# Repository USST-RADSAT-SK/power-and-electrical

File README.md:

# power-and-electrical

## How to Download GitBash
  
  Gitbash is a terminal that you use to execute "git" commands and its highly recommended that you download it 
  
  Use the following link
  https://git-scm.com/downloads
  
## How to Copy a Repo

  Make a folder on your local drive (I make a folder on my desktop)
  
  go into that folder and right click and open gitbash at that location
  
  find the green button in the github that says "Code"
  
  click and copy the URL
  
  go back into the gitbash enter
  
  "git clone [URL]" 

  Now if you want to make changes to a file please make a branch 
  
## How To View a Branch

  Say you want to do a quick check on the progress for the PCB board
  
  use the following commands in git bash
  
  "git checkout [name of branch]"
  
  In the case that KiCad is not updating automatically use the following procedure:
  
  - open project file with "open with..." in file directory 

  If you quickly want to check when the last changes were done to a branch use
  
  "git log"
  
  scroll up & you will see the most recent commit and who did it
  
## How To Make a Branch
  
  a branch is like a copy of files that you can edit on your local drive where you dont have to worry about messing up the main code
  
  make sure you are in the right directory
  
  "git branch [name of the branch]"

  keep the name of the branch short and sweet no need to make it complitcated

## How to Commit a Change

  Once gitbash is opened you want to make sure you are in the right file directory you want to use the command 
  
  "git status"
  
  to check if you saved your files (it will show up as red)
  
  "Git add [filename]"
  
  this will prepare your file to be commited
  
  "git status"
  
  the file name should be green now
  
  "git commit -m "[changes you made as a comment]" "
  
  this will commit your changes 
  
  "git push"
  
  this will save your changes into the branch

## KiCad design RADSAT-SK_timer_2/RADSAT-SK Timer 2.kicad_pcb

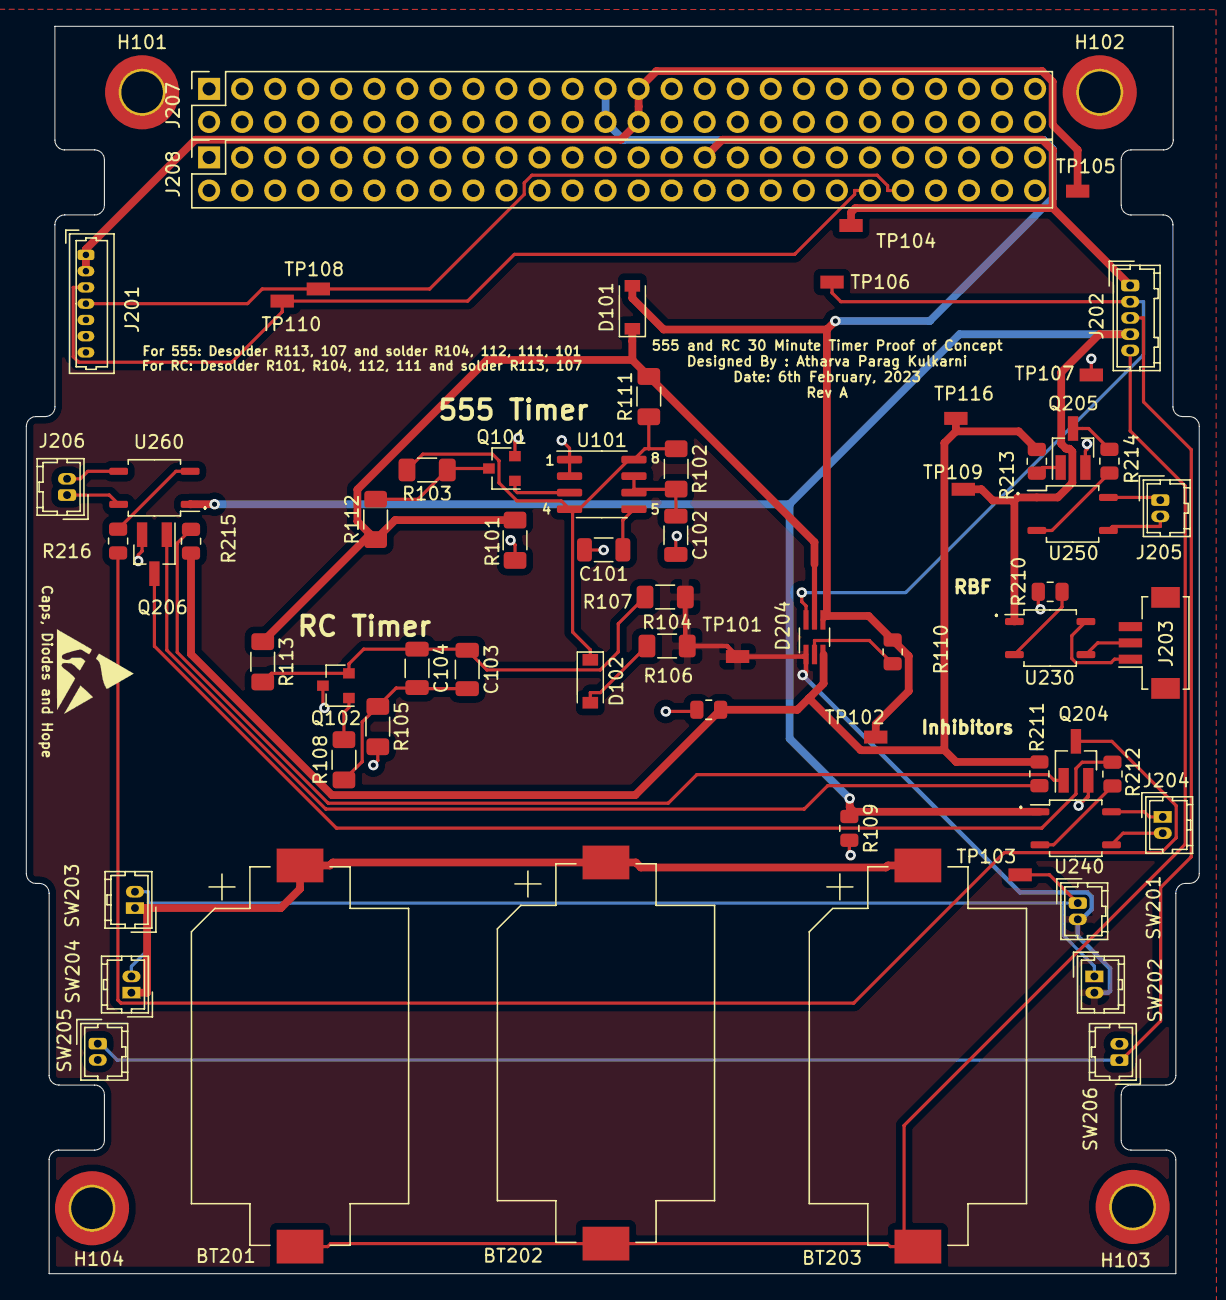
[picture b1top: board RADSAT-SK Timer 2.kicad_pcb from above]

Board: 2 copper layers, 90.2 x 95.9 mm, 69 parts (0 on the bottom side), 43 nets.

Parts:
BT201, BT202, BT203: Battery_Cell; BatteryHolder_Keystone_1060_1x2032
C101: 10nF; C_1206_3216Metric
C102, C103, C104: 600uF; C_1206_3216Metric
D101, D102: SBR80520LT1G; D_SOD-123
D204: BAT54CDW; SOT-363_SC-70-6_Handsoldering
H101, H102, H103, H104: MountingHole; MountingHole_3.2mm_M3_ISO7380_Pad_TopBottom
J201: Conn_01x07; Molex_PicoBlade_53047-0710_1x07_P1.25mm_Vertical
J202: Conn_01x05_Female; Hirose_DF13-05P-1.25DSA_1x05_P1.25mm_Vertical
J203: Conn_01x03; Hirose_DF13C_CL535-0403-5-51_1x03-1MP_P1.25mm_Vertical
J204, J205, J206: Conn_01x02; Hirose_DF13-02P-1.25DSA_1x02_P1.25mm_Vertical
J207, J208: Conn_02x26_Odd_Even; PinSocket_2x26_P2.54mm_Vertical
Q101: 2N7002E; SOT-23
Q102: DSS4240T-7; SOT-23
Q204, Q205, Q206: IRLML2060; SOT-23_Handsoldering
R101: 10k; R_1206_3216Metric_Pad1.30x1.75mm_HandSolder
R102, R108: 3M; R_1206_3216Metric_Pad1.30x1.75mm_HandSolder
R103: 1M; R_1206_3216Metric_Pad1.30x1.75mm_HandSolder
R104, R105, R107, R111, R112, R113: 0; R_1206_3216Metric_Pad1.30x1.75mm_HandSolder
R106, R109: 1M; R_0805_2012Metric
R110: 40; R_0805_2012Metric
R210: 320; R_0805_2012Metric
R211, R213, R215: 25; R_0805_2012Metric
R212, R214, R216: 260; R_0805_2012Metric
SW201, SW202, SW203, SW204, SW205, SW206: SW_Push; Hirose_DF13-02P-1.25DSA_1x02_P1.25mm_Vertical
TP101, TP102, TP103, TP104, TP105, TP106, TP107, TP108, TP109, TP110, TP116: TestPoint; HARWIN_S2761-46R
U101: TLC555CDR; SOIC-8_3.9x4.9mm_P1.27mm
U230, U240, U250, U260: CPC1114N; SOP-4_3.8x4.1mm_P2.54mm

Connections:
+3V3: J201.1, J201.2, J207.27, J207.28, TP105.1
+5V: D101.2, D204.4, J207.25, J207.26, R110.2, TP102.1
+BATT: D204.1, R104.2, R107.2, SW201.2, SW202.2, TP101.1
/Inhib_in: D204.3, R106.1, R211.1, R213.1, R215.1, TP116.1
A: BT201.1, BT202.1, BT203.1, SW203.1, SW204.1
GND: C101.2, C102.2, J201.5, J201.6, J201.7, J207.29, J207.30, J207.32, Q101.2, Q102.3, Q204.2, Q205.2, Q206.2, R101.2, R105.2, R106.2, R109.2, R210.2, SW205.2, SW206.2, TP107.1, U101.1, U101.2
I2C_CLK: J201.4, J208.44, TP108.1
I2C_DATA: J201.3, J208.42, TP110.1
InhibV+: J202.4, R109.1, TP109.1, U230.1, U240.1, U250.1, U260.1
Inhib_EN: D101.1, D204.5, R101.1, R111.2, R112.1, R113.1
unnamed: BT201.2, BT202.2, BT203.2, J202.5
unnamed: C101.1, U101.5
unnamed: C102.1, R102.2, U101.6, U101.7
unnamed: C103.1, C104.1, Q102.2, R107.1, R113.2
unnamed: C103.2, C104.2, R105.1, R108.1
unnamed: D102.1, R102.1, R103.2, R111.1, U101.4, U101.8
unnamed: D102.2, R104.1
unnamed: D204.2, R110.1
unnamed: D204.6, J202.2, TP106.1
unnamed: J202.3, SW205.1, SW206.1
unnamed: J203.1, U230.4
unnamed: J203.2, U230.3
unnamed: J204.1, U240.4
unnamed: J204.2, U240.3
unnamed: J205.1, U250.4
unnamed: J205.2, U250.3
unnamed: J206.1, U260.4
unnamed: J206.2, U260.3
unnamed: Q101.1, U101.3
unnamed: Q101.3, R103.1, R112.2
unnamed: Q102.1, R108.2
unnamed: Q204.1, R215.2
unnamed: Q204.3, R216.2
unnamed: Q205.1, R213.2
unnamed: Q205.3, R214.2
unnamed: Q206.1, R211.2
unnamed: Q206.3, R212.2
unnamed: R210.1, U230.2
unnamed: R212.1, U240.2
unnamed: R214.1, U250.2
unnamed: R216.1, U260.2
unnamed: SW201.1, SW202.1, SW203.2, SW204.2, TP103.1
USB_Charge: J202.1, J208.31, TP104.1

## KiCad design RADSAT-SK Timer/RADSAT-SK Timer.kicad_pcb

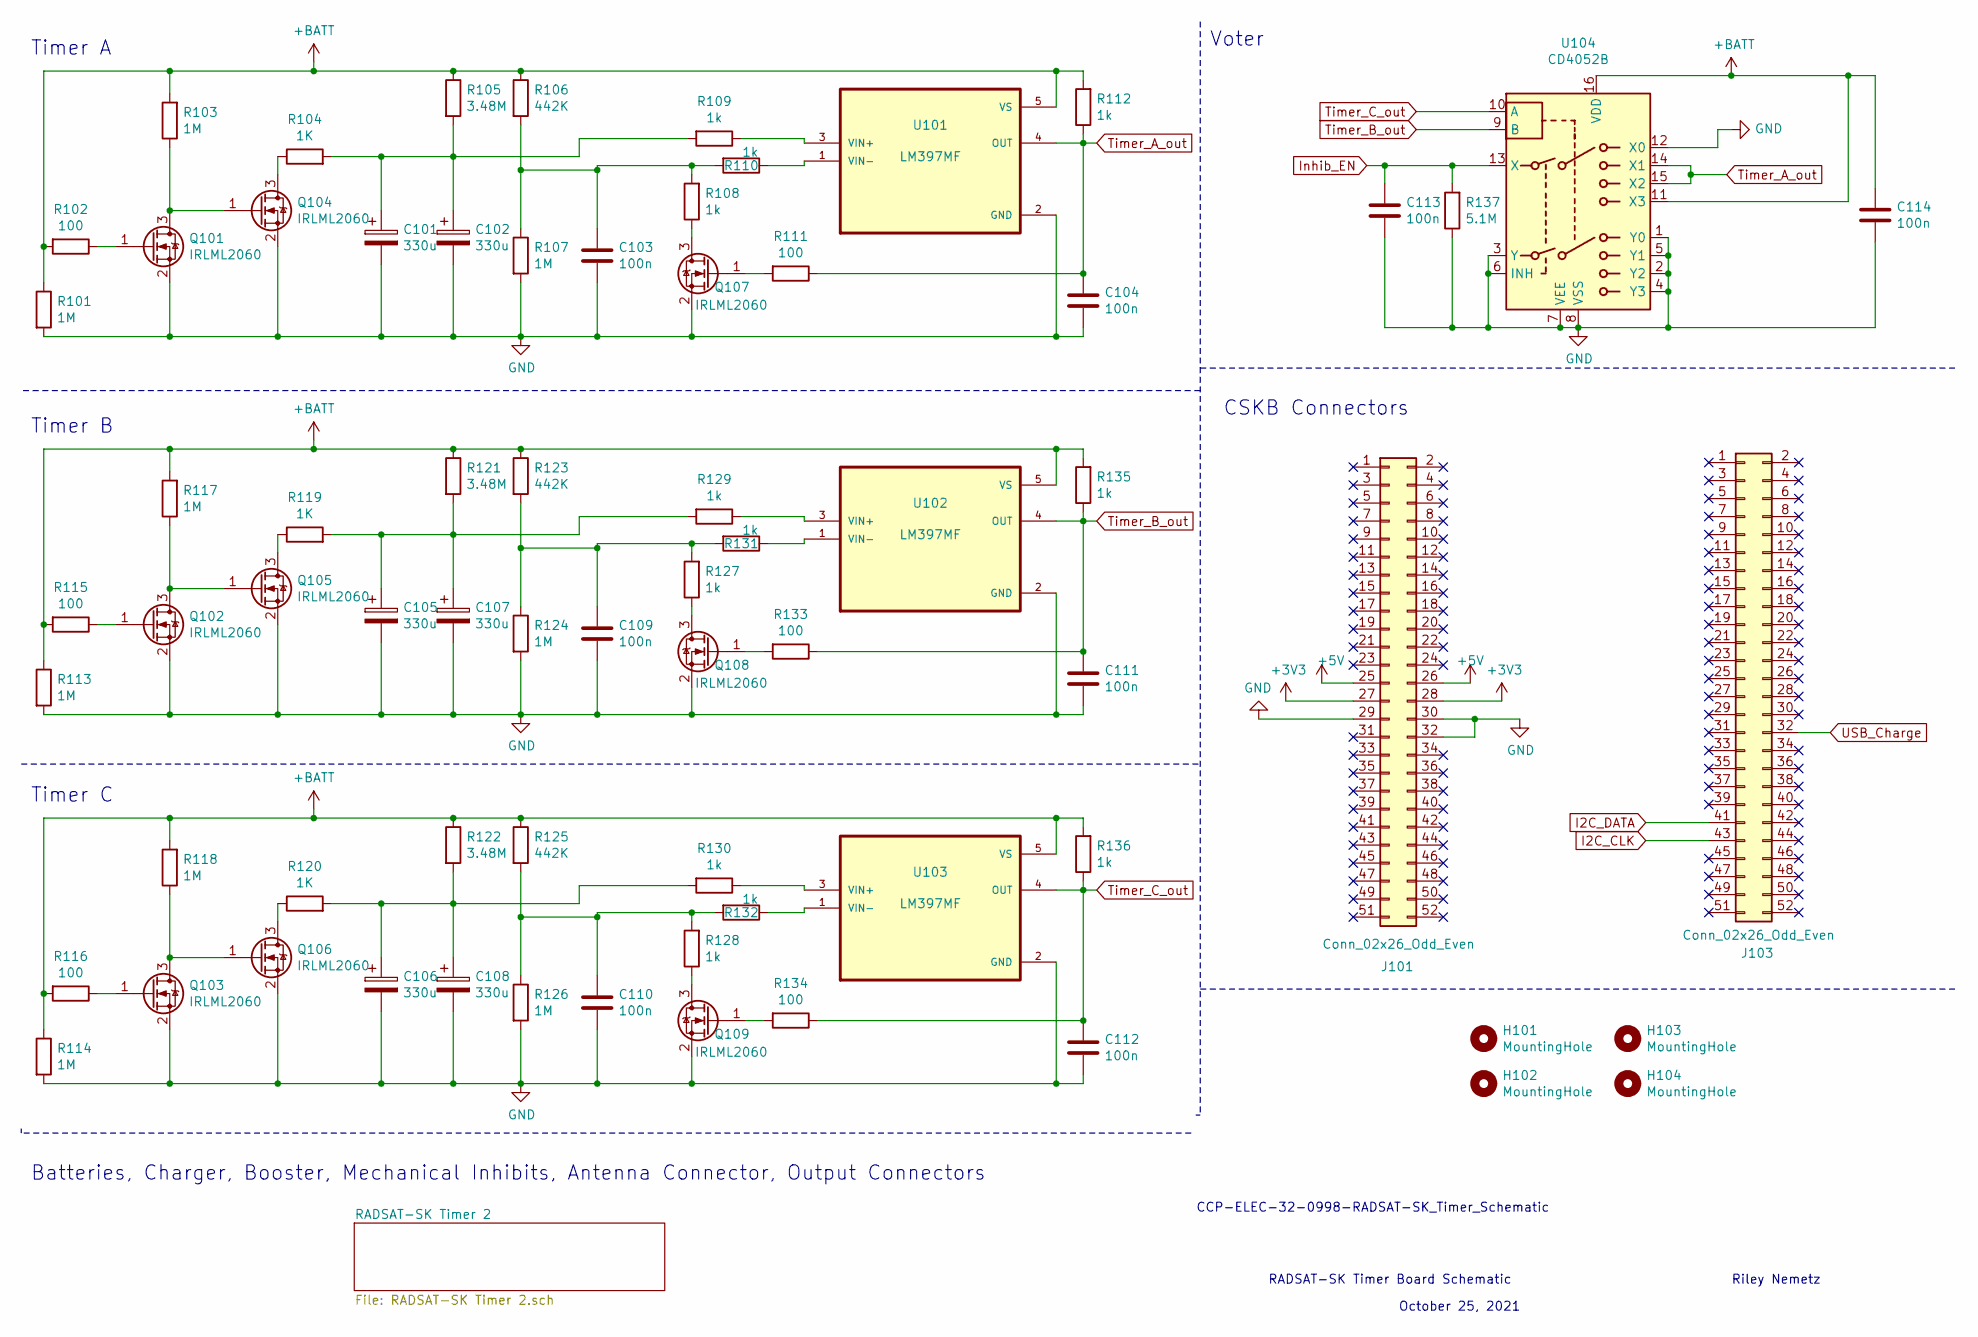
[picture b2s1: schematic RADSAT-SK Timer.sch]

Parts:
C101, C102, C105, C106, C107, C108: 330u; CP_EIA-7343-30_AVX-N_Pad2.25x2.55mm_HandSolder
C103, C104, C109, C110, C111, C112, C113, C114: 100n; C_0805_2012Metric
H101, H102, H103, H104: MountingHole; MountingHole_3.2mm_M3_ISO7380_Pad_TopBottom
J101, J103: Conn_02x26_Odd_Even; PinSocket_2x26_P2.54mm_Vertical
Q101, Q102, Q103, Q104, Q105, Q106, Q107, Q108, Q109: IRLML2060; SOT-23_Handsoldering
R101, R103, R107, R113, R114, R117, R118, R124, R126: 1M; R_0805_2012Metric
R102, R111, R115, R116, R133, R134: 100; R_0805_2012Metric
R104, R119, R120: 1K; R_0805_2012Metric
R105, R121, R122: 3.48M; R_0805_2012Metric
R106, R123, R125: 442K; R_0805_2012Metric
R108, R109, R110, R112, R127, R128, R129, R130, R131, R132, R135, R136: 1k; R_0805_2012Metric
R137: 5.1M; R_0805_2012Metric
U101, U102, U103: LM397MF; TSOT-23-5_HandSoldering
U104: CD4052B; TSSOP-16_4.4x5mm_P0.65mm

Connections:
+3V3: J101.27, J101.28; also elsewhere on the board
+5V: J101.25, J101.26; also elsewhere on the board
+BATT: C114.1, R101.1, R102.2, R103.2, R105.1, R106.1, R112.2, R113.1, R114.1, R115.2, R116.2, R117.2, R118.2, R121.1, R122.1, R123.1, R125.1, R135.2, R136.2, U101.5 (VS), U102.5 (VS), U103.5 (VS), U104.11 (X3), U104.16 (VDD); also elsewhere on the board
GND: C101.2, C102.2, C103.2, C104.2, C105.2, C106.2, C107.2, C108.2, C109.2, C110.2, C111.2, C112.2, C113.2, C114.2, J101.29, J101.30, J101.32, Q101.2 (S), Q102.2 (S), Q103.2 (S), Q104.2 (S), Q105.2 (S), Q106.2 (S), Q107.2 (S), Q108.2 (S), Q109.2 (S), R101.2, R107.2, R113.2, R114.2, R124.2, R126.2, R137.1, U101.2 (GND), U102.2 (GND), U103.2 (GND), U104.1 (Y0), U104.2 (Y2), U104.3 (Y), U104.4 (Y3), U104.5 (Y1), U104.6 (INH), U104.7 (VEE), U104.8 (VSS), U104.12 (X0); also elsewhere on the board
I2C_CLK: J103.43; also elsewhere on the board
I2C_DATA: J103.41; also elsewhere on the board
Inhib_EN: C113.1, R137.2, U104.13 (X); also elsewhere on the board
unnamed: C101.1, C102.1, R104.2, R105.2, R109.2
unnamed: C103.1, R106.2, R107.1, R108.2, R110.2
unnamed: C105.1, C107.1, R119.2, R121.2, R129.2
unnamed: C106.1, C108.1, R120.2, R122.2, R130.2
unnamed: C109.1, R123.2, R124.1, R127.2, R131.2
unnamed: C110.1, R125.2, R126.1, R128.2, R132.2
unnamed: Q101.1 (G), R102.1
unnamed: Q101.3 (D), Q104.1 (G), R103.1
unnamed: Q102.1 (G), R115.1
unnamed: Q102.3 (D), Q105.1 (G), R117.1
unnamed: Q103.1 (G), R116.1
unnamed: Q103.3 (D), Q106.1 (G), R118.1
unnamed: Q104.3 (D), R104.1
unnamed: Q105.3 (D), R119.1
unnamed: Q106.3 (D), R120.1
unnamed: Q107.1 (G), R111.2
unnamed: Q107.3 (D), R108.1
unnamed: Q108.1 (G), R133.2
unnamed: Q108.3 (D), R127.1
unnamed: Q109.1 (G), R134.2
unnamed: Q109.3 (D), R128.1
unnamed: R109.1, U101.3 (VIN+)
unnamed: R110.1, U101.1 (VIN-)
unnamed: R129.1, U102.3 (VIN+)
unnamed: R130.1, U103.3 (VIN+)
unnamed: R131.1, U102.1 (VIN-)
unnamed: R132.1, U103.1 (VIN-)
Timer_A_out: C104.1, R111.1, R112.1, U101.4 (OUT), U104.14 (X1), U104.15 (X2)
Timer_B_out: C111.1, R133.1, R135.1, U102.4 (OUT), U104.9 (B)
Timer_C_out: C112.1, R134.1, R136.1, U103.4 (OUT), U104.10 (A)
USB_Charge: J103.32; also elsewhere on the board

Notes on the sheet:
RADSAT-SK Timer Board Schematic
October 25, 2021
CCP-ELEC-32-0998-RADSAT-SK_Timer_Schematic
Riley Nemetz
Timer A
Voter
CSKB Connectors
Batteries, Charger, Booster, Mechanical Inhibits, Antenna Connector, Output Connectors
Timer B
Timer C

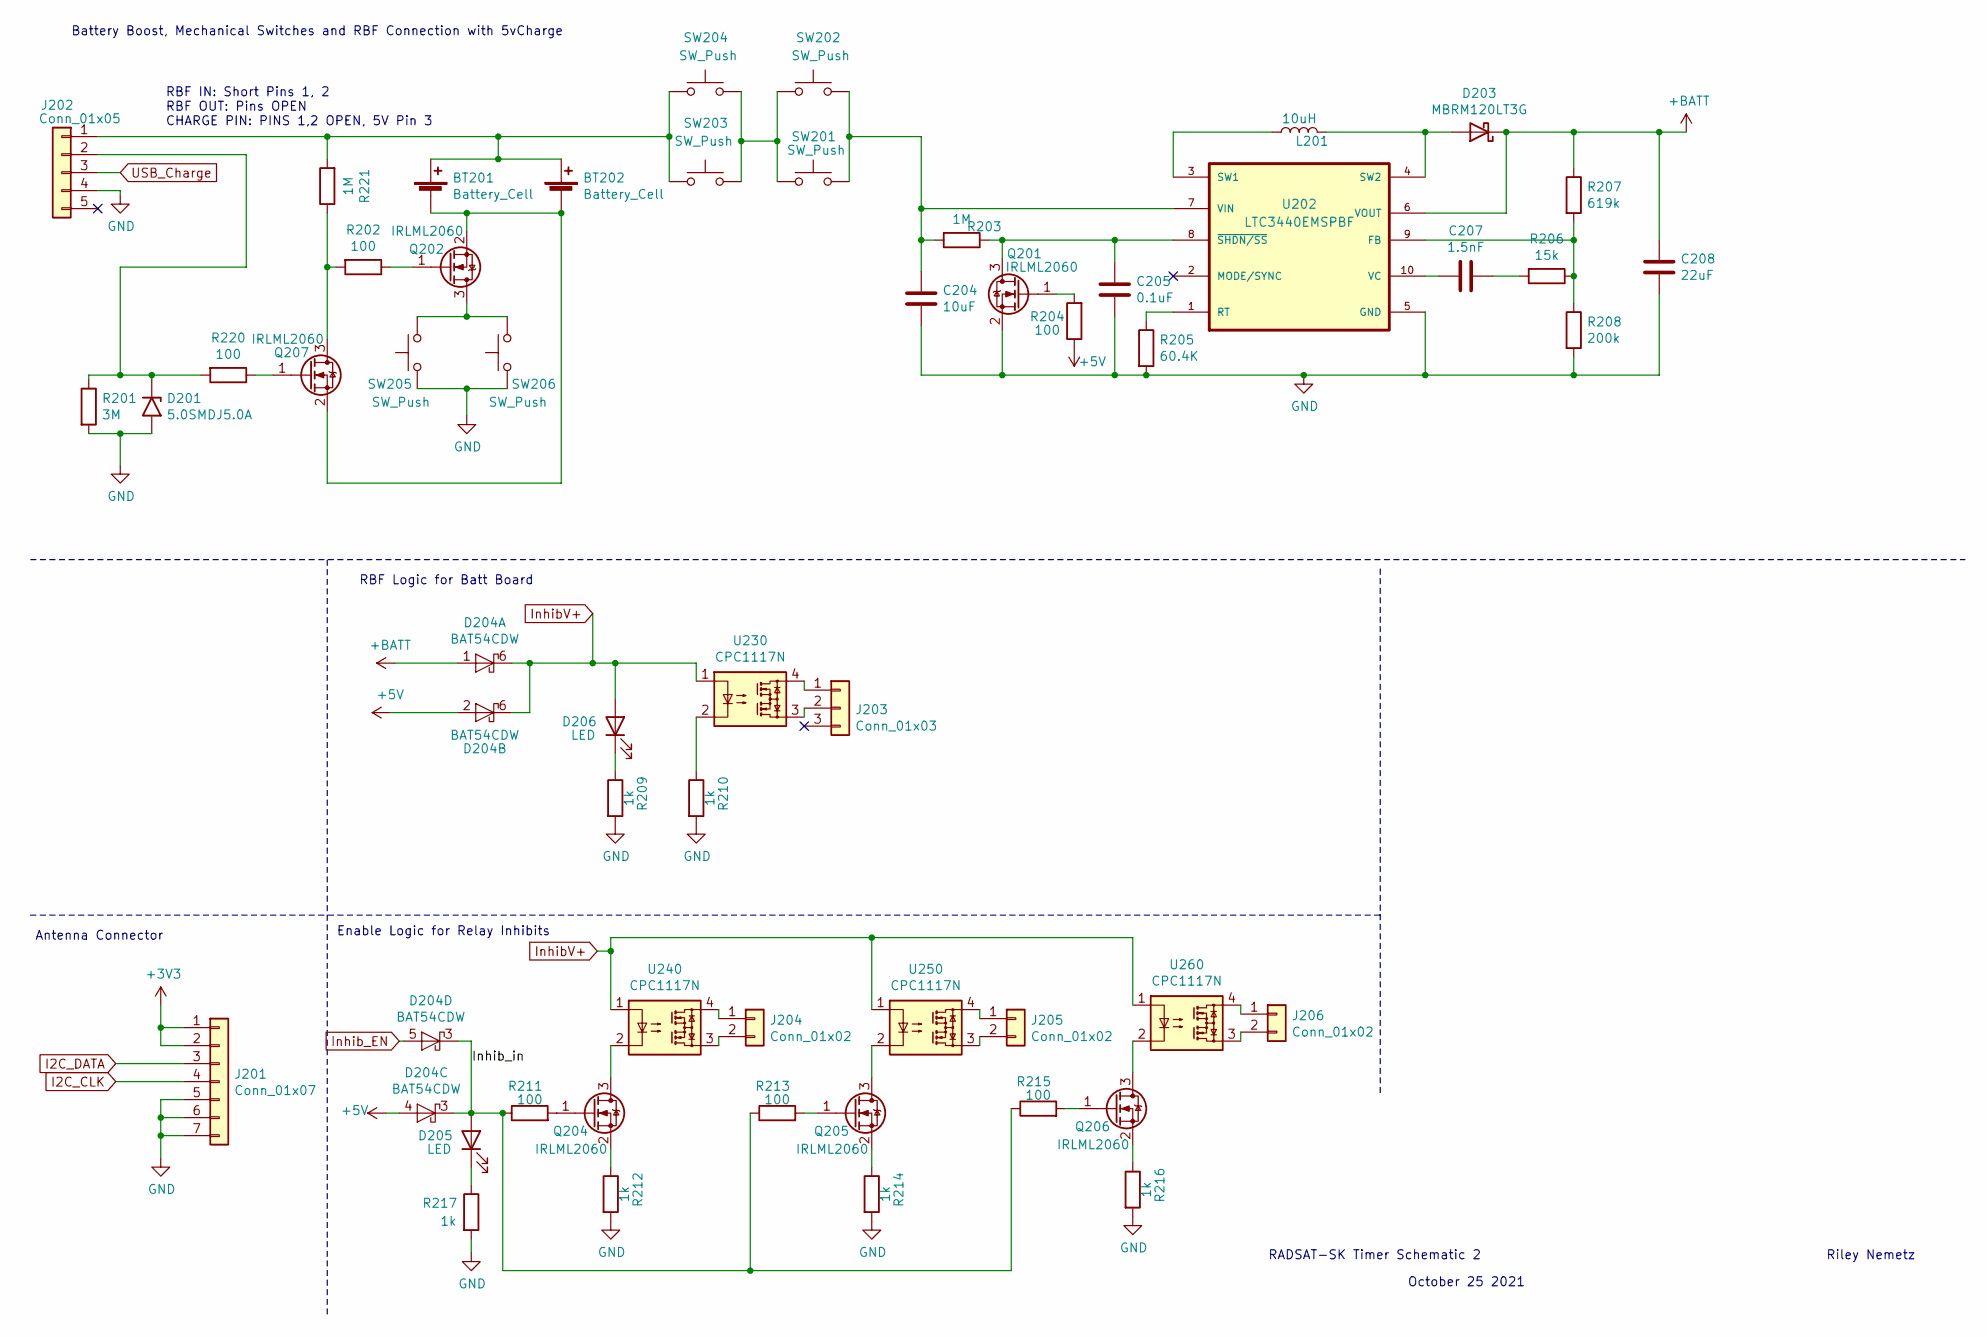
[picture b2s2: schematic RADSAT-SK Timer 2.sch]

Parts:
BT201, BT202: Battery_Cell; BatteryHolder_Keystone_1060_1x2032
C204: 10uF; C_0805_2012Metric
C205: 0.1uF; C_0805_2012Metric
C207: 1.5nF; C_0805_2012Metric
C208: 22uF; C_1210_3225Metric_Pad1.33x2.70mm_HandSolder
D201: 5.0SMDJ5.0A; D_SMC_Handsoldering
D203: MBRM120LT3G; D_Powermite_AK
D204: BAT54CDW; SOT-363_SC-70-6_Handsoldering
D205, D206: LED; LED_0603_1608Metric_Pad1.05x0.95mm_HandSolder
J201: Conn_01x07; Molex_PicoBlade_53047-0710_1x07_P1.25mm_Vertical
J202: Conn_01x05; Hirose_DF13-05P-1.25DSA_1x05_P1.25mm_Vertical
J203: Conn_01x03; Hirose_DF13C_CL535-0403-5-51_1x03-1MP_P1.25mm_Vertical
J204, J205, J206: Conn_01x02; Hirose_DF13-02P-1.25DSA_1x02_P1.25mm_Vertical
L201: 10uH; Sumida_inductor
Q201, Q202, Q204, Q205, Q206, Q207: IRLML2060; SOT-23_Handsoldering
R201: 3M; R_0805_2012Metric
R202, R204, R211, R213, R215, R220: 100; R_0805_2012Metric
R203, R221: 1M; R_0805_2012Metric
R205: 60.4K; R_0805_2012Metric
R206: 15k; R_0805_2012Metric
R207: 619k; R_0805_2012Metric
R208: 200k; R_0805_2012Metric
R209, R210, R212, R214, R216, R217: 1k; R_0805_2012Metric
SW201, SW202, SW203, SW204, SW205, SW206: SW_Push; Hirose_DF13-02P-1.25DSA_1x02_P1.25mm_Vertical
U202: LTC3440EMSPBF; MSOP-10_3x3mm_P0.5mm; MPN LTC3440EMS#PBF
U230, U240, U250, U260: CPC1117N; SOP-4_3.8x4.1mm_P2.54mm

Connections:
+3V3: J201.1, J201.2; also elsewhere on the board
+5V: D204.2 (A), D204.4 (A), R204.1; also elsewhere on the board
+BATT: C208.1, D203.1 (K), D204.1 (A), R207.1, U202.6 (VOUT); also elsewhere on the board
/RADSAT-SK Timer 2/Inhib_in: D204.3 (K), D205.2 (A), R211.1, R213.1, R215.1
GND: C204.2, C205.2, C208.2, D201.2 (A2), J201.5, J201.6, J201.7, J202.4, Q201.2 (S), R201.2, R205.2, R208.2, R209.2, R210.2, R212.2, R214.2, R216.2, R217.2, SW205.1, SW206.1, U202.5 (GND); also elsewhere on the board
I2C_CLK: J201.4; also elsewhere on the board
I2C_DATA: J201.3; also elsewhere on the board
InhibV+: D204.6 (K), D206.2 (A), U230.1, U240.1, U250.1, U260.1
Inhib_EN: D204.5 (A); also elsewhere on the board
unnamed: BT201.1 (+), BT202.1 (+), J202.1, R221.2, SW203.1, SW204.1
unnamed: BT201.2 (-), BT202.2 (-), Q202.2 (S), Q207.2 (S)
unnamed: C204.1, R203.2, SW201.2, SW202.2, U202.7 (VIN)
unnamed: C205.1, Q201.3 (D), R203.1, U202.8 (~SHDN/SS)
unnamed: C207.1, R206.2
unnamed: C207.2, U202.10 (VC)
unnamed: D201.1 (A1), J202.2, R201.1, R220.2
unnamed: D203.2 (A), L201.2, U202.4 (SW2)
unnamed: D205.1 (K), R217.1
unnamed: D206.1 (K), R209.1
unnamed: J203.1, U230.4
unnamed: J203.2, U230.3
unnamed: J204.1, U240.4
unnamed: J204.2, U240.3
unnamed: J205.1, U250.4
unnamed: J205.2, U250.3
unnamed: J206.1, U260.4
unnamed: J206.2, U260.3
unnamed: L201.1, U202.3 (SW1)
unnamed: Q201.1 (G), R204.2
unnamed: Q202.1 (G), R202.1
unnamed: Q202.3 (D), SW205.2, SW206.2
unnamed: Q204.1 (G), R211.2
unnamed: Q204.2 (S), R212.1
unnamed: Q204.3 (D), U240.2
unnamed: Q205.1 (G), R213.2
unnamed: Q205.2 (S), R214.1
unnamed: Q205.3 (D), U250.2
unnamed: Q206.1 (G), R215.2
unnamed: Q206.2 (S), R216.1
unnamed: Q206.3 (D), U260.2
unnamed: Q207.1 (G), R220.1
unnamed: Q207.3 (D), R202.2, R221.1
unnamed: R205.1, U202.1 (RT)
unnamed: R206.1, R207.2, R208.1, U202.9 (FB)
unnamed: R210.1, U230.2
unnamed: SW201.1, SW202.1, SW203.2, SW204.2
USB_Charge: J202.3; also elsewhere on the board

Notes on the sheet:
Riley Nemetz
Battery Boost, Mechanical Switches and RBF Connection with 5vCharge
RADSAT-SK Timer Schematic 2
Antenna Connector
Enable Logic for Relay Inhibits
October 25 2021
RBF IN: Short Pins 1, 2 RBF OUT: Pins OPEN CHARGE PIN: PINS 1,2 OPEN, 5V Pin 3
RBF Logic for Batt Board

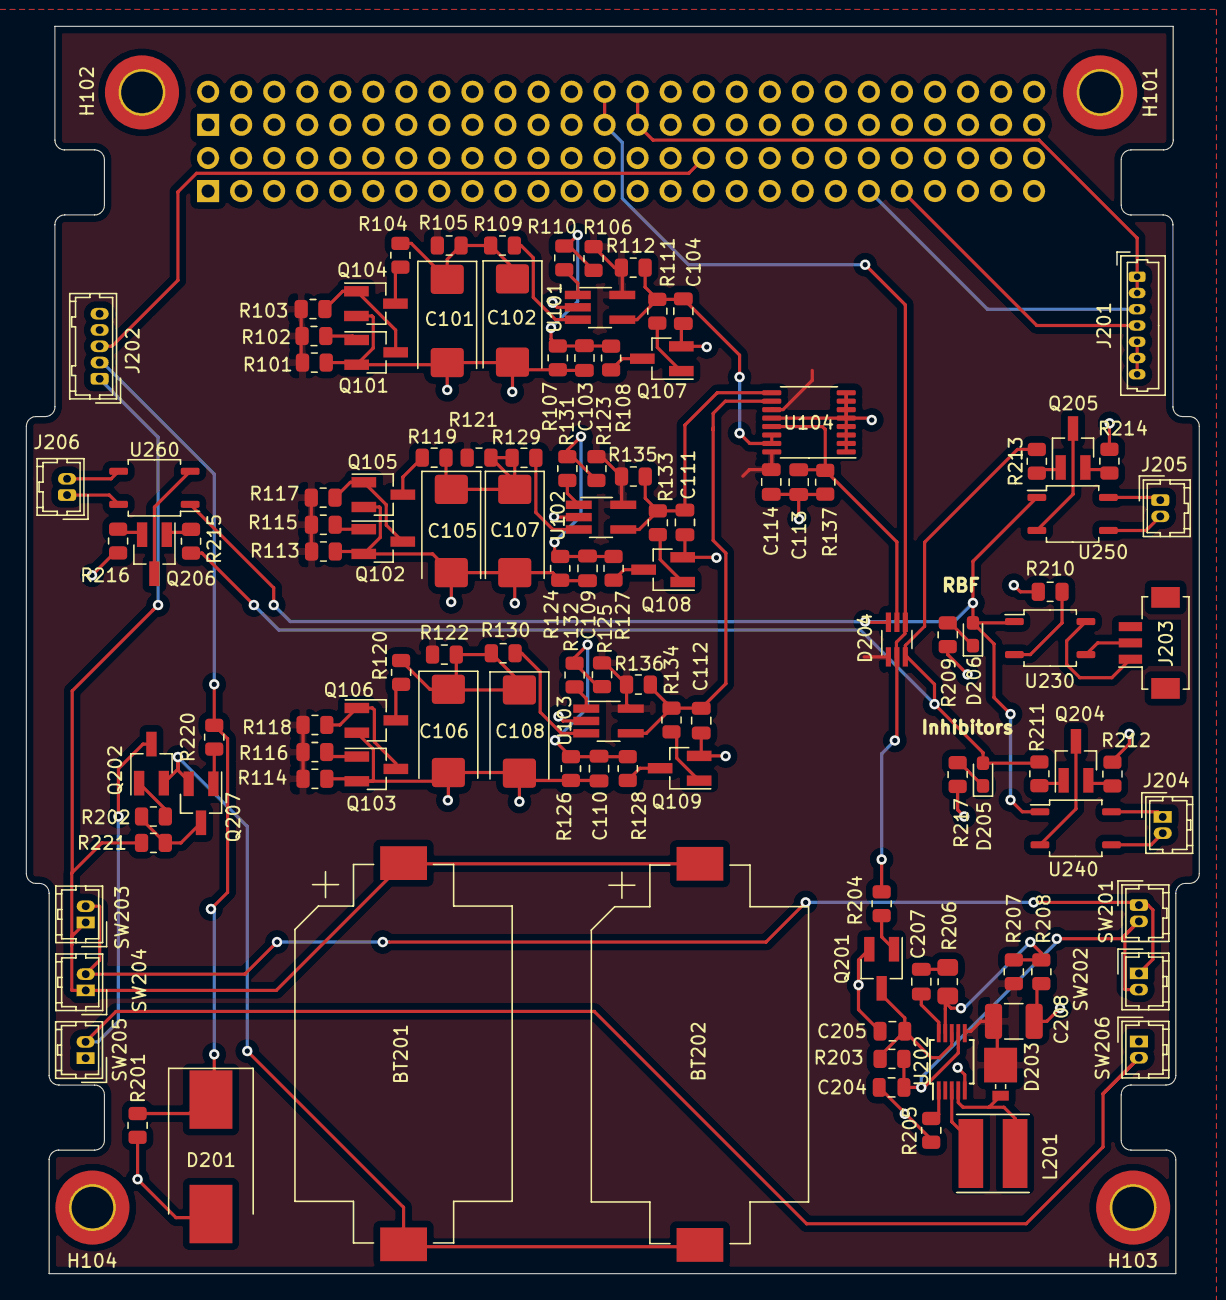
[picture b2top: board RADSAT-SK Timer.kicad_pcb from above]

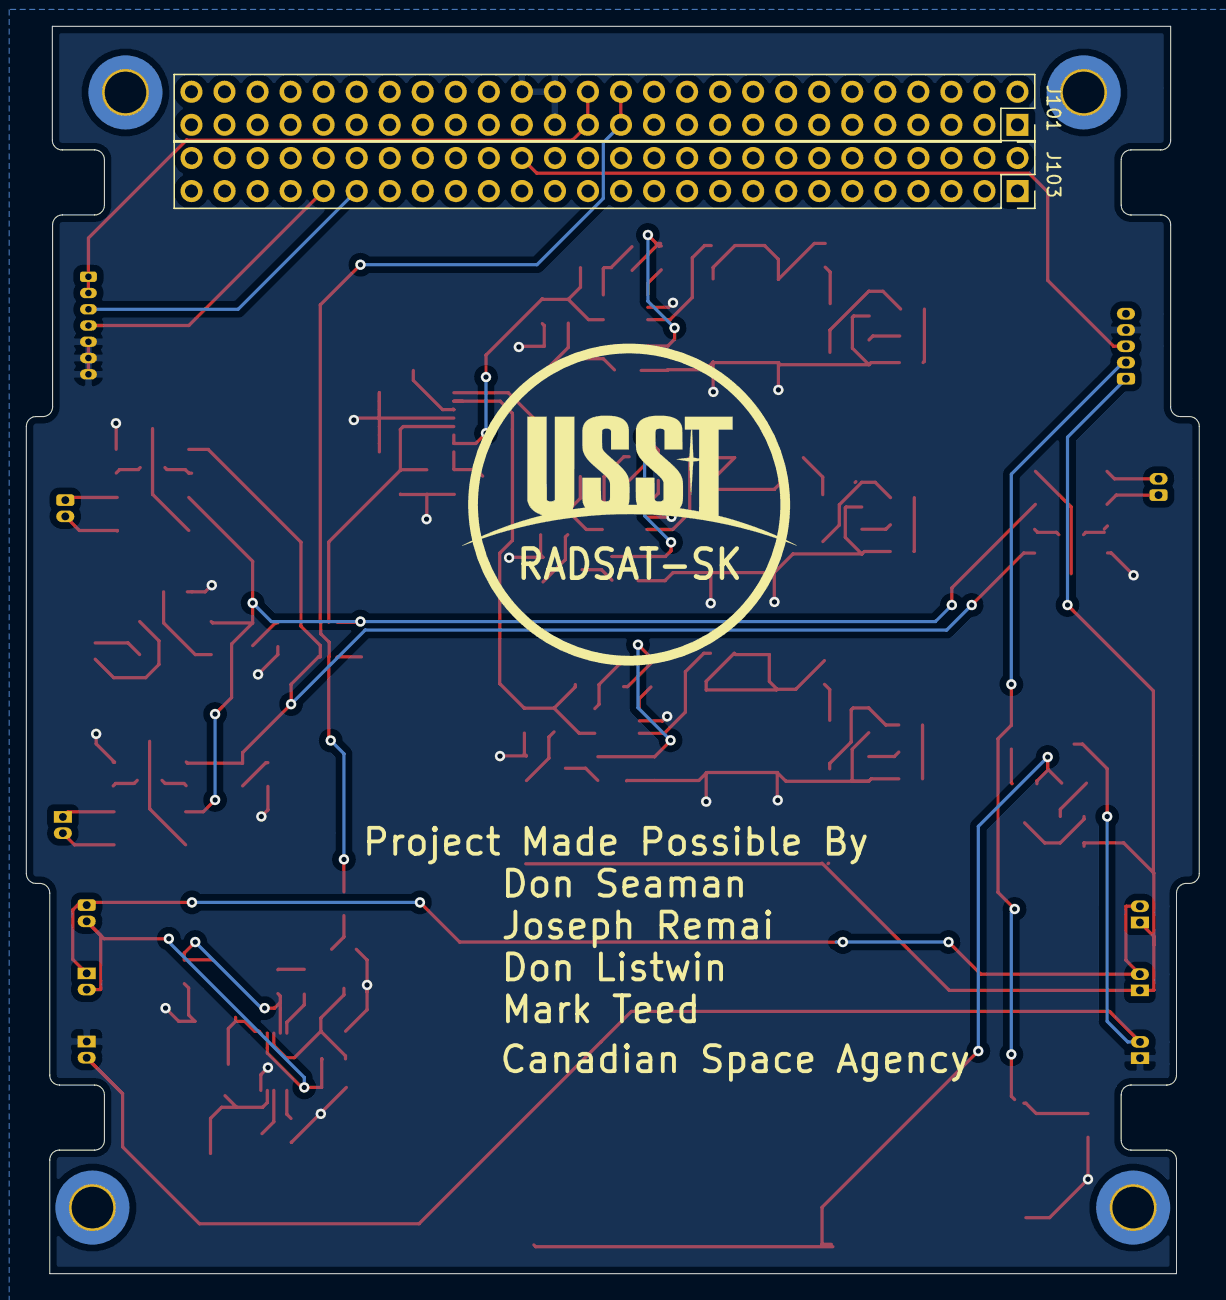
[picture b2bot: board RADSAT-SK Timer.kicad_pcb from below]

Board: 2 copper layers, 90.2 x 95.9 mm, 124 parts (2 on the bottom side), 77 nets.

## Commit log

2021-05-26 added default files from dropbox
2021-05-27 PCB has been resized and the layer redone to fit the new shape, assumed a cent red stack for the main connector. No rounded edges.
2021-06-01 figured out how to do rounded corners also pull request test
2021-06-01 Rounded corners X24
2021-06-02 Pc bresize (#7)
    * PCB has been resized and the layer redone to fit the new shape, assumed a cent red stack for the main connector. No rounded edges.
    * figured out how to do rounded corners also pull request test
    * Rounded corners X24
2021-06-15 deleted files for a battery holder that we are not using, -had added it myself- rearanged some of the layout to get outer edge for ports, changed to df13 hirose ports, added dummy usb connector.
2021-07-02 Schematic: Added- 2 more inhibit ports Added- RBF Ports In and Out Connected USb Charger to connector H1-32. Layout: Port positioning and adjustments to some existing circuitry for better tracing.
2021-07-02 schematic saved with above changes
2021-07-03 Retraced the board
2021-08-25 added starting place for RBF timer
2021-09-10 Mason has updated some footprints
2021-09-12 Change to the 7 pin Antenna on the PCB
2021-09-14 added RBF stuff to PCB
2021-09-16 moved some traces
2021-09-16 Retrace (#8)
    * Schematic: Added- 2 more inhibit ports Added- RBF Ports In and Out Connected USb Charger to connector H1-32. Layout: Port positioning and adjustments to some existing circuitry for better tracing.
    * schematic saved with above changes
    * Retraced the board
    * added starting place for RBF timer
    * Mason has updated some footprints
    * Change to the 7 pin Antenna on the PCB
2021-09-16 Revert "Retrace (#8)"
    This reverts commit b83679d15abd0ed1c357c8fd6e32726f91c1f504.
2021-09-16 Revert "Retrace (#8)" (#9)
    This reverts commit b83679d15abd0ed1c357c8fd6e32726f91c1f504.
2021-09-16 Retrace (#10)
    * Schematic: Added- 2 more inhibit ports Added- RBF Ports In and Out Connected USb Charger to connector H1-32. Layout: Port positioning and adjustments to some existing circuitry for better tracing.
    * schematic saved with above changes
    * Retraced the board
    * added starting place for RBF timer
    * Mason has updated some footprints
    * Change to the 7 pin Antenna on the PCB
2021-09-25 Revert "Retrace (#8)" (#11)
    This reverts commit b83679d15abd0ed1c357c8fd6e32726f91c1f504.
2021-09-25 Deleted a bunch of backups and unnecessary project files
2021-09-25 Added in the RBF connector and setup to coincells, need to add inhibitor logic and find components
2021-09-26 1.Added USB Header, Footprint and lib files 2. got rid of the rescue library by reassigning the symbols to proper libraries in the project 3. assigned footprints to all components, though BOM still M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
2021-09-26 PCBheader layout version 1, Note Main Bus Headers are on back of PCB to line pin 1 with batt board, RBF output is 3pin??? Need proper allignment of Main header
2021-09-27 Added missing Capacitor value from old schematic in the slack discussion
2021-10-01 Cleaned Up the USb footprint and updated the libraries to play nice with KiCad
2021-10-01 More Library management, added text to pcb to identify easily connectors, Added a cool custom USST RADSAT-SK Logo to the project, may need to be scaled down or placed on back of board
2021-10-13 JFET
2021-10-16 added pchannel JFET and Diode logic for inhibitors, edited the layout a bit still not final
2021-10-21 formatted a BOM and added datasheet urls from previous BOM on the dropbox. Quite dissapointed that like only 2 components were actually sourced and there are no digikey/mouser links associated with a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
2021-10-21 Added some more components to the BOM, Still need to figure out HIROSE Connectors, would like to use 2 pin instead of 3 pin. Took forever to figure out the antenna connector that was used
2021-10-22 More components to the BOM and fixed footprints on the schematic to mathc chosen parts
2021-10-22 This commit contains more ccomponent sourcing, mainly a diode array for the inhibitor logic diodes, handsoldering footprints have been chosen for some of the sourced components, see BOM, this should 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
2021-10-24 use of a C117 solid state relay and another mosfet for isolated connection of the pins ie we dont care about the pin characteristic now baby
2021-10-25 actually did the other relays for the inhibits, played around with layout stuff
2021-10-25 Adjusted the BOM to refelct previosu changes, made the 3d Model of the layout look good, swapped the antenna and the usb charger to other sides of the boards
2021-10-26 Noticed that the source on all of the schematic 2 transistors were wrong and needed to be flipped, except on the rbf where it is intentional q Q ~
2021-10-27 Sourced coin cell battery and tantalum caps, still need to footprint coin cell holders
2021-10-28 the RBF relay transistor was redundant, added in another LED and updated diode configuration, resistor sourcing TBD
2021-10-28 need to go bakc to previos zener diode for overvoltage
2021-10-28 This contains a completed BOM, Still need to create the Inductor footprint and add sponsor names/logo, then can get into retracing this sucker
2021-10-29 better layour for timer components
2021-10-30 Made changes to accomadate the RBF alternate charge plug
2021-11-02 single wire was missing, final commit before merging to main
2021-11-02 RBF Circuit was modified and new components added to BOM
2021-11-03 Timer circuit layouts, next up is buck booster
2021-11-06 Layout ios near complete just need to make custom inductor footprint
2021-11-08 Modified Inductor Footprint, fixed 3d Model orientation, generated gerbers and drill files. Still unsure about ESD Protection, but can simply remove components from board later.
2021-12-14 added CSA to the list of donors
2022-01-15 added link for CSKB and created zip folder for gerbers
2022-02-21 Added a folder for the LTSpice Sims
2022-03-03 Added Folder for LTSpice Simulations Added a new csv file for TIMB BOM generated by KiCad
2022-03-09 Improved RBF_logic and made LTSpice it a working simulation
2022-03-09 Added buck booster logic LTSpice verification
2022-03-10 Added LTspice file for RBF Battery Board Inhibit logic
2022-03-11 Added file for Enable RBF logic
2022-04-15 changed the name of relay on schematic
2022-04-15 Chaned solder pad dimentions of replacement 15k resistor, R206
2022-05-21 changes to RBF logic LT sim to include the exact MOSFET
2022-05-21 added file for buck boost +rbf inhibit
2022-05-21 added working buck boost and RBF circuits
2022-06-04 added KiCad design folder for 555 timer
2022-06-04 deleted corrupt 555 timer file and created new blank file
2022-06-07 added second timerboard file for new design
2022-06-08 Added files for LTSpice simulations of the 3rd timerboard design (The third design is called TIMB 2)
2022-06-08 added simulations of the second timerboard logic
2022-06-11 changed RBF logic and added footprint for J202
2022-06-12 Tracing and PCB design for the new TMIB rev 1
2022-06-14 renamed PCB file
2022-06-19 new RBF logic and charging circuit!!
2022-06-19 annotated part numbers (generated netlist)
2022-06-20 switched out pin 3 and 5 on RBF pin
2022-06-20 fixed RBF logic (back to initial state) and added test points
2022-06-20 deleted extra LEDs
2022-06-21 added pull down resistors on relays
2022-06-23 added resistors in schematic, changed Voltage regulator
2022-06-23 routed PCB
2022-06-23 added test points
2022-06-26 added galaxia timer in schematic, made footprint for galaxia timer and added to PCB new
2022-06-27 fixed traces
2022-06-29 swapped antenna connector and RBF port, pushed switches closer to the coin cells and moved silk screen out of vias
2022-06-29 fulled in back copper
2022-07-02 places resistor above FET and rerouted PCB
2022-07-03 fixed CSKB footprint placement
2022-07-03 LTSpcie for current divider
2022-07-03 fixed relay connection and routed through hole resistor for current divider
2022-07-03 modified LT chip sim with current divider
2022-07-03 PERFECTLY alligned the CSKB connectors
2022-07-03 corrected I2C CSKB trace
2022-07-03 addded R values
2022-07-04 final touches
2022-07-05 gave traces breathing room along the galaxia timer
2023-02-06 trying to fix "?" in schematic error
2023-02-08 555 push for production
